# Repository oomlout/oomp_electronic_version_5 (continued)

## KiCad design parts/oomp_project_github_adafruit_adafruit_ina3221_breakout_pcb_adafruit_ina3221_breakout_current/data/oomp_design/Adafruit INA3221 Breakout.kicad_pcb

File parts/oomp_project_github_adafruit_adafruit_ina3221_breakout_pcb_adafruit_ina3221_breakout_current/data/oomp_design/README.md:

# OOMP KiCad design copy

Open `Adafruit INA3221 Breakout.kicad_pro` (or the `.kicad_pcb` / `.kicad_sch`) in KiCad. Local OOMP libraries are under `libraries/`. Original inputs are preserved in [../original/](../original/).

Only verified unchanged installed KiCad defaults were renamed. Modified, custom, unmatched and unavailable items remain unchanged. Soldering variants are never swapped during conversion. Existing pad coordinates, nets and UUIDs are preserved.

See [conversion_report.yaml](conversion_report.yaml) for every conversion and skip. Copy this directory before editing; regeneration refuses to overwrite edited design files.

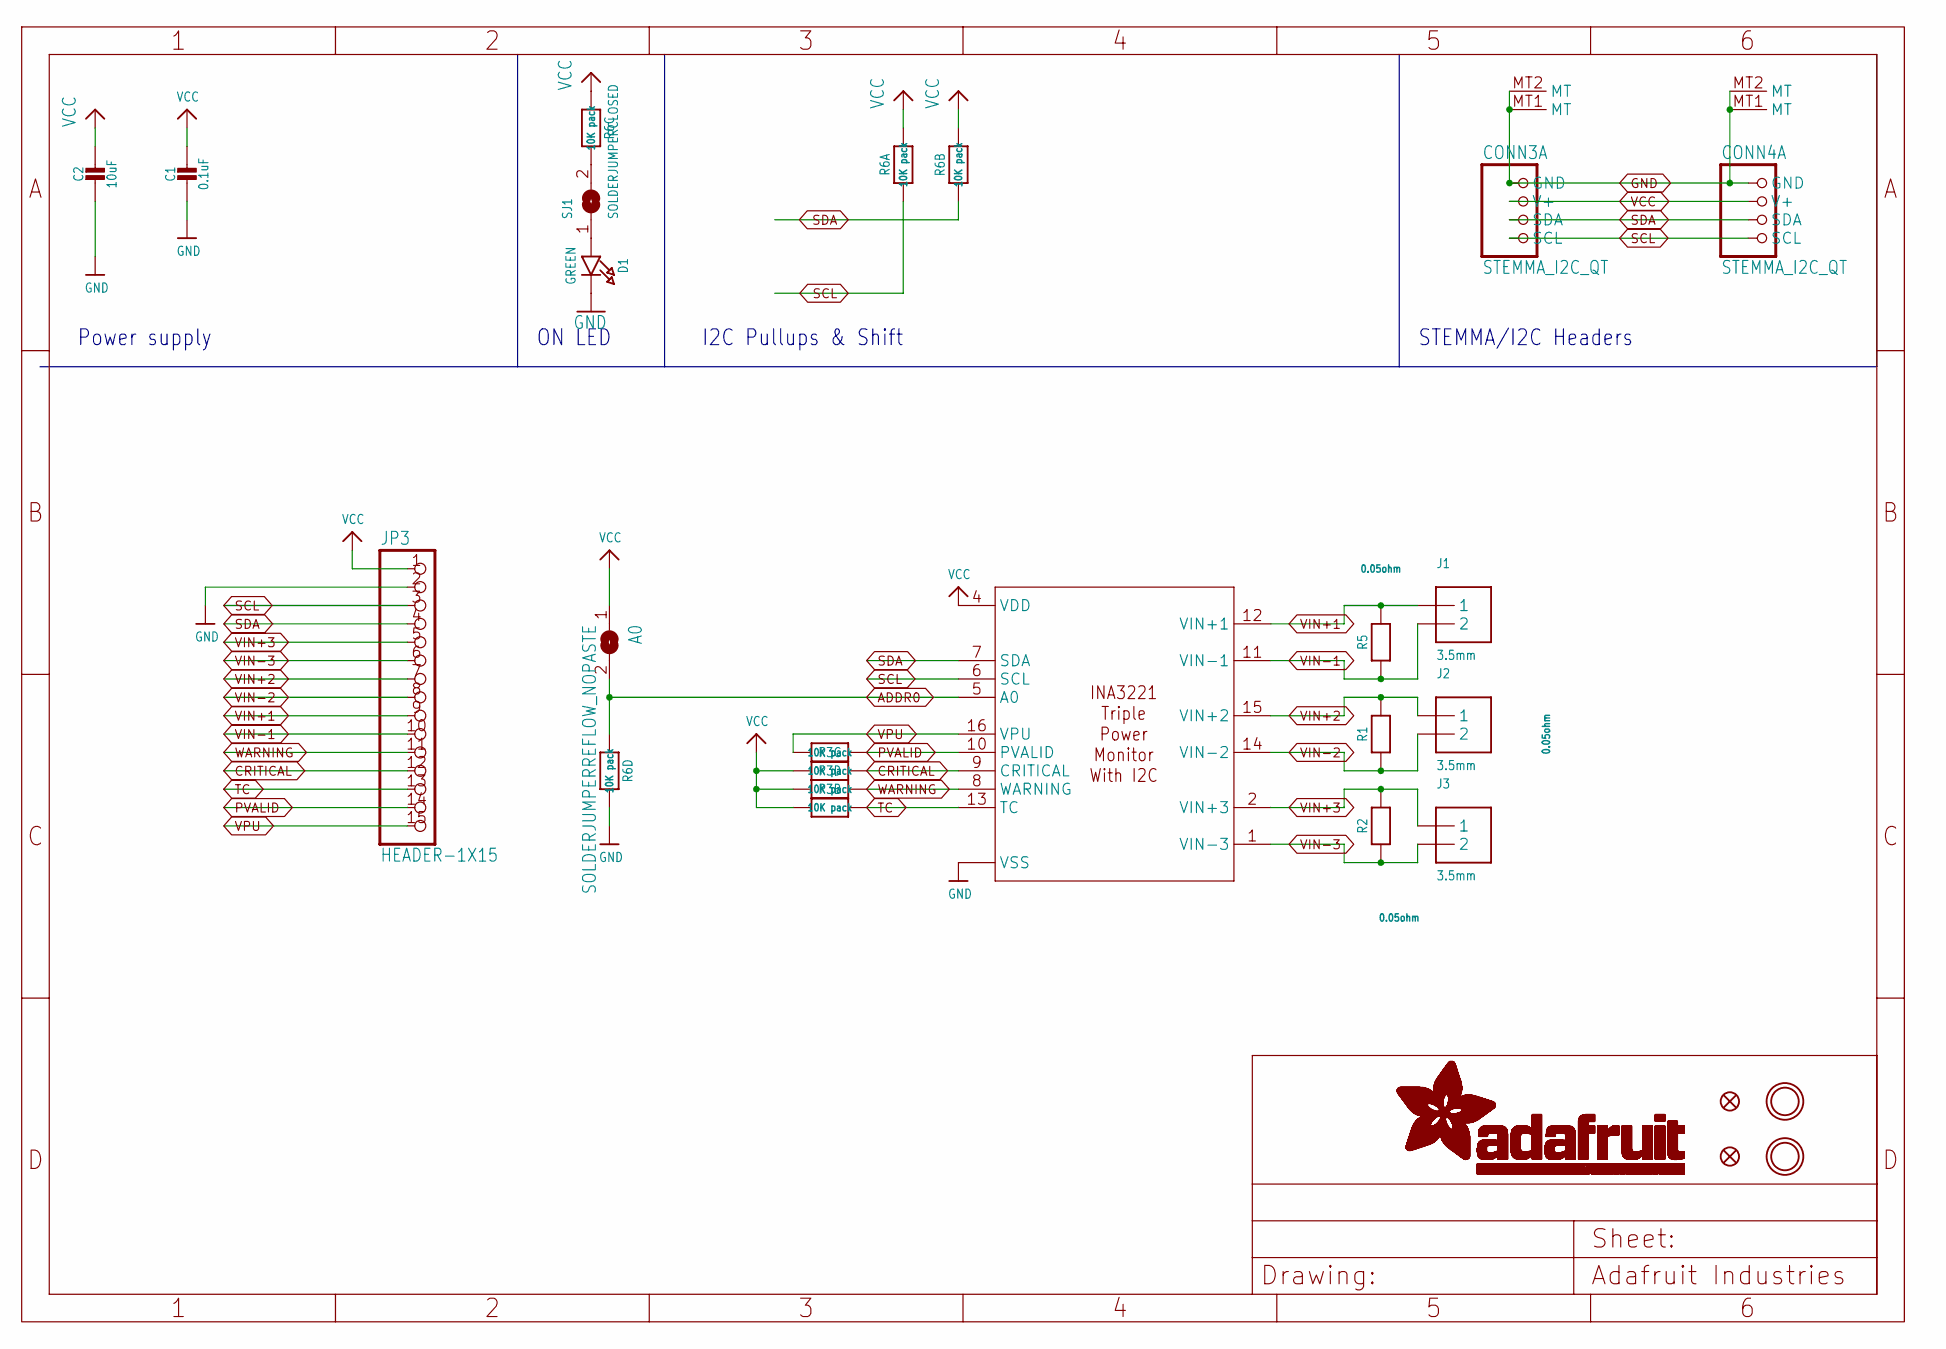
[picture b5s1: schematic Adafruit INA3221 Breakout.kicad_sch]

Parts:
A0: SOLDERJUMPERREFLOW_NOPASTE; SOLDERJUMPER_REFLOW_NOPASTE
C1: 0.1uF; 0603-NO
C2: 10uF; 0805-NO
CONN3, CONN4: STEMMA_I2C_QT; JST_SH4; LCSC C2845363
D1: GREEN; CHIPLED_0603_NOOUTLINE
FID3, FID4: FIDUCIAL_1MM
IC1: INA3221; PVQFN-16
J1, J2, J3: 3.5mm; TERMBLOCK_1X2-3.5MM
JP3: HEADER-1X15; 1X15_ROUND_70
R1, R2, R5: 0.05ohm; _1206
R3, R6: 10K pack; RESPACK_4X0603
SJ1: SOLDERJUMPERCLOSED; SOLDERJUMPER_CLOSEDWIRE
U$20, U$21: MOUNTINGHOLE2.5; MOUNTINGHOLE_2.5_PLATED

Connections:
ADDR0: A0.2, IC1.5 (A0), R6.4 (1)
CRITICAL: IC1.9 (CRITICAL), JP3.12, R3.6 (2)
GND: C1.2, C2.2, CONN3.1 (GND), CONN3.MT1 (MT), CONN3.MT2 (MT), CONN4.1 (GND), CONN4.MT1 (MT), CONN4.MT2 (MT), D1.C, IC1.3 (VSS), IC1.P$18 (VSS), IC1.P$19 (VSS), IC1.P$20 (VSS), IC1.P$21 (VSS), IC1.P$22 (VSS), IC1.THERMAL (VSS), JP3.2, R6.5 (2)
unnamed: R6.6 (2), SJ1.2
unnamed: D1.A, SJ1.1
PVALID: IC1.10 (PVALID), JP3.14, R3.8 (2)
SCL: CONN3.4 (SCL), CONN4.4 (SCL), IC1.6 (SCL), JP3.3, R6.1
SDA: CONN3.3 (SDA), CONN4.3 (SDA), IC1.7 (SDA), JP3.4, R6.2 (1)
TC: IC1.13 (TC), JP3.13, R3.7 (2)
VCC: A0.1, C1.1, C2.1, CONN3.2 (V+), CONN4.2 (V+), IC1.4 (VDD), JP3.1, R3.2 (1), R3.3 (1), R3.4 (1), R6.3 (1), R6.7 (2), R6.8 (2)
VIN+1: IC1.12 (VIN+1), J1.1, JP3.9, R5.2
VIN+2: IC1.15 (VIN+2), J2.1, JP3.7, R1.2
VIN+3: IC1.2 (VIN+3), J3.1, JP3.5, R2.2
VIN-1: IC1.11 (VIN-1), J1.2, JP3.10, R5.1
VIN-2: IC1.14 (VIN-2), J2.2, JP3.8, R1.1
VIN-3: IC1.1 (VIN-3), J3.2, JP3.6, R2.1
VPU: IC1.16 (VPU), JP3.15, R3.1
WARNING: IC1.8 (WARNING), JP3.11, R3.5 (2)

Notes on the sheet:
STEMMA/I2C Headers
Power supply
ON LED
I2C Pullups & Shift

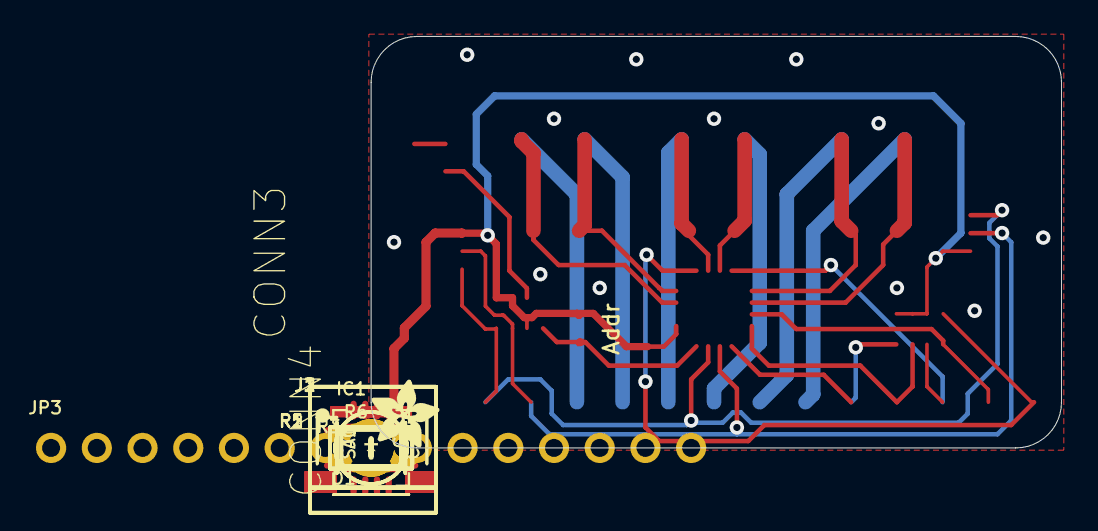
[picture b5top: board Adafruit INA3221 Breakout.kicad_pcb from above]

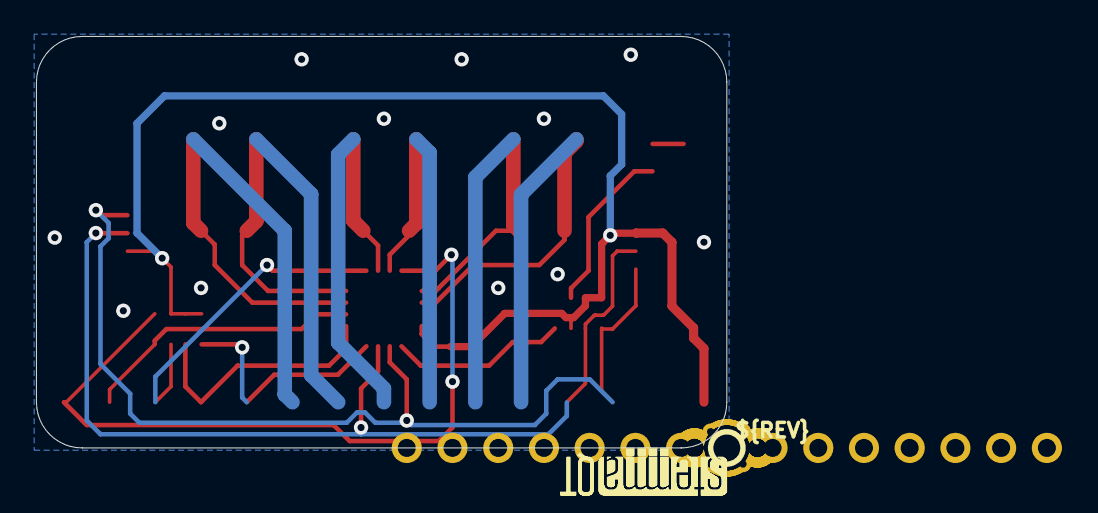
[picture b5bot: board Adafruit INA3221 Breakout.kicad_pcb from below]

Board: 2 copper layers, 38.4 x 22.9 mm, 54 parts (7 on the bottom side), 18 nets.

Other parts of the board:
PLABEL0: PLABEL0
PLABEL1: PLABEL1
PLABEL2: PLABEL2
PLABEL3: PLABEL3
PLABEL4: PLABEL4
PLABEL5: PLABEL5
PLABEL6: PLABEL6
PLABEL7: PLABEL7
PLABEL8: PLABEL8
PLABEL9: PLABEL9
PLABEL10: PLABEL10
PLABEL11: PLABEL11
PLABEL12: PLABEL12
PLABEL13: PLABEL13
PLABEL14: PLABEL14
PLABEL15: PLABEL15
PLABEL16: PLABEL16
PLABEL17: PLABEL17
PLABEL18: PLABEL18
PLABEL19: PLABEL19
PLABEL20: PLABEL20
PLABEL21: PLABEL21
PLABEL22: PLABEL22
PLABEL23: PLABEL23
PLABEL24: PLABEL24
PLABEL25: PLABEL25
PLABEL26: PLABEL26
PLABEL27: PLABEL27
PLABEL28: PLABEL28
U$7: ADAFRUIT_3.5MM
U$30: PCBFEAT-REV-040
U$31, U$32: STEMMAQT

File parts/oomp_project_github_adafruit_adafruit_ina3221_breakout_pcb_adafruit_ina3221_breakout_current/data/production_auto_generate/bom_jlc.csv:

Comment,Designator,Footprint,LCSC Part #
,JP3,Adafruit INA3221 Breakout-import-fps:1X15_ROUND_70,C7501589
,U$7,Adafruit INA3221 Breakout-import-fps:ADAFRUIT_3.5MM,
,U$30,Adafruit INA3221 Breakout-import-fps:PCBFEAT-REV-040,
,PLABEL0,Adafruit INA3221 Breakout-import-fps:PLABEL0,
,PLABEL1,Adafruit INA3221 Breakout-import-fps:PLABEL1,
,PLABEL10,Adafruit INA3221 Breakout-import-fps:PLABEL10,
,PLABEL11,Adafruit INA3221 Breakout-import-fps:PLABEL11,
,PLABEL12,Adafruit INA3221 Breakout-import-fps:PLABEL12,
,PLABEL13,Adafruit INA3221 Breakout-import-fps:PLABEL13,
,PLABEL14,Adafruit INA3221 Breakout-import-fps:PLABEL14,
,PLABEL15,Adafruit INA3221 Breakout-import-fps:PLABEL15,
,PLABEL16,Adafruit INA3221 Breakout-import-fps:PLABEL16,
,PLABEL17,Adafruit INA3221 Breakout-import-fps:PLABEL17,
,PLABEL18,Adafruit INA3221 Breakout-import-fps:PLABEL18,
,PLABEL19,Adafruit INA3221 Breakout-import-fps:PLABEL19,
,PLABEL2,Adafruit INA3221 Breakout-import-fps:PLABEL2,
,PLABEL20,Adafruit INA3221 Breakout-import-fps:PLABEL20,
,PLABEL21,Adafruit INA3221 Breakout-import-fps:PLABEL21,
,PLABEL22,Adafruit INA3221 Breakout-import-fps:PLABEL22,
,PLABEL23,Adafruit INA3221 Breakout-import-fps:PLABEL23,
,PLABEL24,Adafruit INA3221 Breakout-import-fps:PLABEL24,
,PLABEL25,Adafruit INA3221 Breakout-import-fps:PLABEL25,
,PLABEL26,Adafruit INA3221 Breakout-import-fps:PLABEL26,
,PLABEL27,Adafruit INA3221 Breakout-import-fps:PLABEL27,
,PLABEL28,Adafruit INA3221 Breakout-import-fps:PLABEL28,
,PLABEL3,Adafruit INA3221 Breakout-import-fps:PLABEL3,
,PLABEL4,Adafruit INA3221 Breakout-import-fps:PLABEL4,
,PLABEL5,Adafruit INA3221 Breakout-import-fps:PLABEL5,
,PLABEL6,Adafruit INA3221 Breakout-import-fps:PLABEL6,
,PLABEL7,Adafruit INA3221 Breakout-import-fps:PLABEL7,
,PLABEL8,Adafruit INA3221 Breakout-import-fps:PLABEL8,
,PLABEL9,Adafruit INA3221 Breakout-import-fps:PLABEL9,
,A0,Adafruit INA3221 Breakout-import-fps:SOLDERJUMPER_REFLOW_NOPASTE,
,"U$31,U$32",Adafruit INA3221 Breakout-import-fps:STEMMAQT,
0.05ohm,"R1,R2,R5",Adafruit INA3221 Breakout-import-fps:_1206,
0.1uF,C1,Adafruit INA3221 Breakout-import-fps:0603-NO,C14663
10K pack,"R3,R6",Adafruit INA3221 Breakout-import-fps:RESPACK_4X0603,C98220
10uF,C2,Adafruit INA3221 Breakout-import-fps:0805-NO,
3.5mm,"J1,J2,J3",Adafruit INA3221 Breakout-import-fps:TERMBLOCK_1X2-3.5MM,
GREEN,D1,Adafruit INA3221 Breakout-import-fps:CHIPLED_0603_NOOUTLINE,
INA3221,IC1,Adafruit INA3221 Breakout-import-fps:PVQFN-16,
STEMMA_I2C_QT,"CONN3,CONN4",Adafruit INA3221 Breakout-import-fps:JST_SH4,C160404
